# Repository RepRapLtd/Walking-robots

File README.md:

# Walking-robots

This repository contains all our work on various walking robots.

But the main item here is a set of enhancements to the Petoi Bittle walking robot. If you click on the link Petoi above that will give you more details of that.

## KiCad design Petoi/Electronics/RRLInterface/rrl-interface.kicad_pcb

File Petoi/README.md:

# RepRap Ltd Upgrades to the Petoi Bittle Walking Robot

The [Petoi Bittle Robot Dog](https://www.petoi.com/pages/bittle-open-source-bionic-robot-dog) is a servo driven quadruped robot with an Arduino controller. But it also allows you to turn the Arduino inside it off and instead plug in a Raspberry Pi. This allows much more sophisticated control with essentially no space limitations on the size of the software driving the robot.

Here is the experimental modified robot on it's development stand. Yes - we know the wires need to be tidied...

We have plugged in a WiFi Raspberry Pi Zero and connected up a small PCB of our own. As you can see we have also replaced the lower legs and the robot's original head with 3D printed ones.

The enhancements that we are in the process of making are:

1. Hall effect foot sensors, so the robot knows when its feet touch down.
2. Gold contacts on the feet, so the robot can find a charging mat and recharge itself automatically.
3. A small OLED display to convey information. On boot, this gives the robot's IP address.
4. The Pi's camera mounted on the head.
5. A LIDAR rangefinder, also on the head.

All these (except the camera) works using the Pi/Petoi's I2C interface.

This is very much work-in-progress, so the mechanical, electronic and software design WILL all change. But if you want to see what we have so far, the main items are:

1. Electronics/RRLInterface/ - the Kicad design for our custom PCB
2. Mechanics/Head Camera and Lidar Mount.FCStd - the FreeCAD design for the neck/head
3. Mechanics/Forearm/v3/ - the lower leg design with the Hall sensor
4. Software/TeachableMachine/ - AI vision to find the charging mat (see [Teachable Machine here](https://teachablemachine.withgoogle.com/))
5. Software/Pi/ - the Python control software for everything non-AI

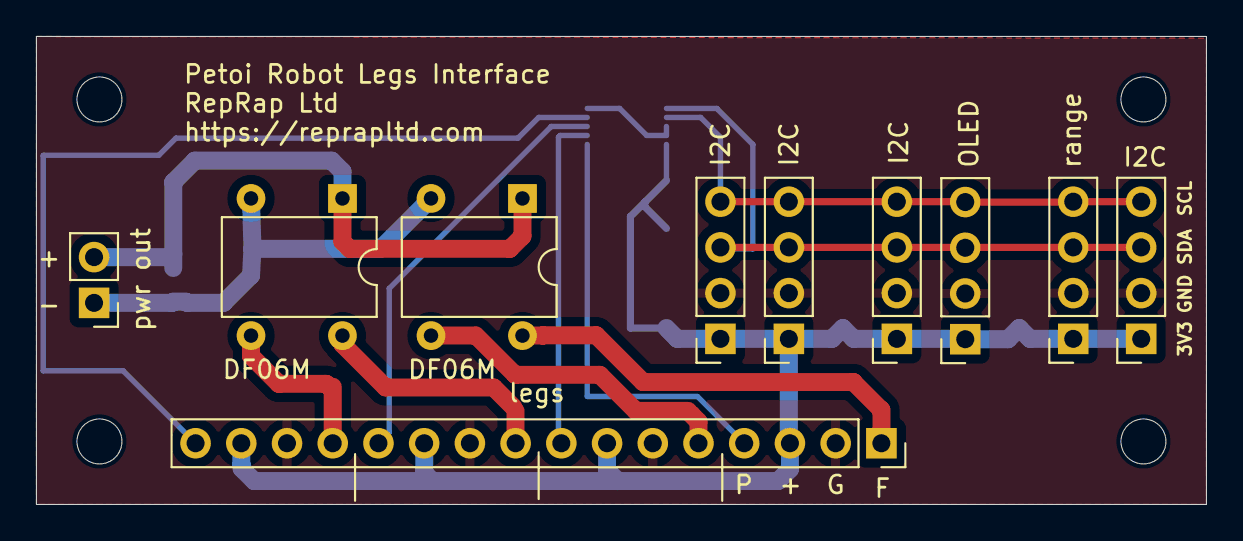
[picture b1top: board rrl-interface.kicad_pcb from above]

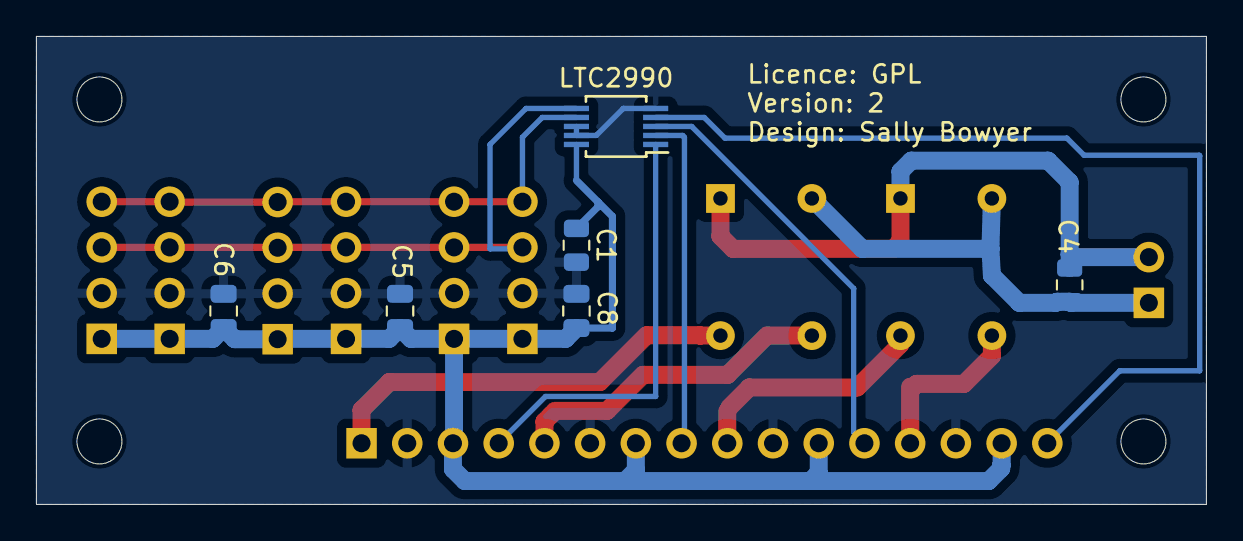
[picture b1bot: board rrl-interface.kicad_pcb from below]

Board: 2 copper layers, 65.0 x 26.0 mm, 20 parts (6 on the bottom side), 14 nets.

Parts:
C1, C5, C6, C8: 0.1u; C_0805_2012Metric
C4: 1u; C_0805_2012Metric
D1, D2: DF06M; Diode_Bridge_DIP-4_W7.62mm_P5.08mm
H1, H2, H3, H4: MountingHole; MountingHole_2.5mm
J1: Legs; PinSocket_1x16_P2.54mm_Vertical
J2: USB pwr out; PinHeader_1x02_P2.54mm_Vertical
J3, J4, J5, J8: I2C; PinSocket_1x04_P2.54mm_Vertical
J6: range; PinSocket_1x04_P2.54mm_Vertical
J7: OLED; PinSocket_1x04_P2.54mm_Vertical
U1: LTC2990; MSOP-10_3x3mm_P0.5mm

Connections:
+3V3: C1.1, C5.1, C6.1, C8.1, J1.3, J1.7, J1.11, J1.15, J3.1, J4.1, J5.1, J6.1, J7.1, J8.1, U1.10
GND: C1.2, C5.2, C6.2, C8.2, J1.2, J1.6, J1.10, J1.14, J3.2, J4.2, J5.2, J6.2, J7.2, J8.2, U1.5, U1.8, U1.9
unnamed: C4.1, D1.2, D2.2, J2.1
unnamed: C4.2, D1.1, D2.1, J2.2
unnamed: D1.3, J1.5
unnamed: D1.4, J1.1
unnamed: D2.3, J1.13
unnamed: D2.4, J1.9
unnamed: J1.4, U1.1
unnamed: J1.8, U1.2
unnamed: J1.12, U1.3
unnamed: J1.16, U1.4
SCL: J3.4, J4.4, J5.4, J6.4, J7.4, J8.4, U1.7
SDA: J3.3, J4.3, J5.3, J6.3, J7.3, J8.3, U1.6

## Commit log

2022-02-17 First commit.
2022-02-17 Added OpenCat submodule.
2022-02-17 Added i2cdevlib submodule
2022-03-09 Foot power circuit added. RRL-OpenCat created with everything in a flat single folder as a single Arduino project for ease of editing.
2022-03-14 Sally's design for a leg force sensor added.
2022-04-01 Sally's latest leg design.
2022-04-08 Imposing sensible directory structure. Sally's latest forearm design. Forearm calibration.
2022-04-25 Teachable machine image recognition experiment added.
2022-04-26 Timing tests.
2022-05-04 Sally's updated designs.
2022-05-05 Final(?) version of Sally's interface PCB.
2022-05-11 Sally's latest design for the leg PCB.
2022-05-20 Keeping things up to date
2022-05-26 Starting work on the Pi Zero code for the I2C robot control.
2022-05-26 Trying out code from https://github.com/rfrht/ltc2990
2022-05-26 Updated AtoD driver to Python3
2022-05-26 Minor correction
2022-06-14 Updated A to D reading program to loop reporting leg hall probe voltages on Leg 1.
2022-06-17 Added 0.91 inch OLED display.
    See: https://www.waveshare.com/wiki/0.91inch_OLED_Module
    C works. Python don't...
2022-06-23 New design of neck added.
2022-09-07 Tidying up and briefly documenting the Pi Zero peripherals.
2022-09-08 Starting work on IP address display.
2022-09-08 Mechanical design update.
2022-09-08 IP address display working.
2022-09-08 Tidying
2022-09-16 PCP spacers.
2022-10-13 Updating README.
2022-10-17 Added servo test program.
2022-10-17 Moved doc into docs...
2022-10-17 Accelerometer test programme added.
2022-10-17 Tidied Python code README.
2022-10-18 Corrected IP display program.
2022-10-18 Servo calibration program written.
2022-10-18 Various servo utilities created.
2022-10-19 Python leg kinematics program added.
2022-10-20 Started work on leg move class.
2022-10-20 More on X Y leg positioning.
2022-10-20 Fix errors.
2022-10-20 Leg movement seems to be working.
2022-10-21 Making legs classier...
2022-10-21 Bug fixes...
2022-10-21 Now with added comments... Plus design for Oled holder
2022-10-21 Debugging...
2022-10-21 Tidying.
2022-10-21 Correction.
2022-10-23 Started to add timesharing to the robot classes so they can all work asynchronously.
2022-10-23 Trivial debugging
2022-10-24 Leg row movement added.
2022-10-24 Fixing bugs...
2022-10-24 Timer fixed (?)
2022-10-25 Correcting zeros - WIP
2022-10-26 A to D code added to leg class for the foot.
2022-10-26 Debugged
2022-10-31 Testing the A to D. Bit slow...
2022-10-31 Switched A to D to continuous mode.
2022-10-31 Bug fix.
2022-10-31 Code tidying
2022-10-31 Rearranging stuff more sensibly.
2022-10-31 Debugging
2022-11-01 README for Petoi project.
2022-11-01 Image update
2022-11-01 Image update again
2022-11-01 Petoi README.md
2022-11-01 README
2022-11-01 Typos
2022-11-01 WIP - Whiptail based robot testing system
2022-11-02 Whiptail WIP
2022-11-02 First hack at menu-driven robot control program.
2022-11-03 More on control prog WIP
2022-11-04 Added a row class. WIP
2022-11-09 Leg row added.
2022-11-09 Debugging WIP
2022-11-14 Tidying/debugging
2022-11-16 more debug
2022-11-16 1st working version (maybe...)
2022-11-17 Added robot class for the whole robot.
2022-11-17 Added other robot sensors to the test program.
2022-11-17 Testing...
2022-11-21 VL53L0X code modified to optionally prevent it sending loads of diagnostics to stdout. #define is in platform/inc/vl53l0x_platform.h
2022-11-21 Sorting out the rangefinder so it doesn't write loads of rubbish to stdout.
2022-11-21 Added stuff to README on how to prevent rangefinder writing loads of guff to stdout.
2022-11-21 Added crude pictures made from ASCII characters to check the camera.
2022-11-21 Crude camera monitoring with text array added.
2022-11-22 New head design. Added code to scan ranges.
2022-11-22 Range picture code added
2022-12-12 Sally improved PCB
2023-01-20 Updating electronics
2023-01-23 Started work on web-based control.
2023-01-26 More work on web interface
2023-01-26 More debugging
2023-01-26 Sally's latest edits
2023-01-26 More Sally code.
2023-01-27 Testing new server.
2023-02-06 More web controller work...
2023-02-08 More messing about with the robot web interface.
2023-02-09 Small example web robot control prog (ahw.php) now works.
2023-02-09 Adding functionality to Sally's single page application.
2023-02-10 Further work on the web interface.
2023-02-14 Web interface WIP.
2023-02-14 More WIP.
2023-02-16 First partly working version?
2023-02-16 First partly working version...
2023-02-16 Don't git the python cache...
2023-02-17 Sally tidying comments.
2023-05-02 Spelling...
2023-05-03 Sally added get voltage function.
2023-06-01 Added simple accelerometer and range monitoring.
2023-06-08 Row code WIP
2024-01-03 Starting work* on a graphical simulator for the Petoi robot.
    * GPT4 doing the heavy lifting. Life is short...
2024-01-04 Robot graphical simulator WIP.
2024-01-04 WIP...
2024-01-05 WIP - first reasonably working version.
2024-01-05 More WIP...
2024-01-08 Initial Pygame version complete. But far too slow for lots of polygons...
2024-01-08 Now with VTK. This seems more promising.
2024-02-28 Updated README with instructions on running the web-based controler.
2024-02-29 Added camera streaming example program.
2024-02-29 Smol edit
2024-03-13 Working on the camera.
2024-03-13 Camera WIP
2024-03-13 Fixed typos
2024-03-16 Threading the camera stream.
2024-03-16 New camera server
2024-03-16 A working version! Thanks GPT4...
2024-03-16 Now records IP to be used for the image.
2024-03-16 This time correctly...
2024-03-17 New LIDAR/Camera mount
2024-03-27 Stable working version.
2024-03-27 Trying (!) to combine the camera and robot servers into one.
2024-03-28 Fixes...
2024-03-28 More GPT4 suggestions...
2024-03-28 Working version. CTRL-C doesn't stop it properly though...
2024-04-03 Robot leg row path input added in a separate file for the moment. Written by GPT4...
2024-04-03 GPT4 conversation that created the grid-input.html webpage and Javascript program added for interest.
2024-04-04 Incorporate leg row grid in main webpage.
2024-04-05 Added screenshots to the GPT4 conversation.

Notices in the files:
Petoi/Electronics/RRLInterface/rrl-interface.kicad_pcb:
Licence: GPL
